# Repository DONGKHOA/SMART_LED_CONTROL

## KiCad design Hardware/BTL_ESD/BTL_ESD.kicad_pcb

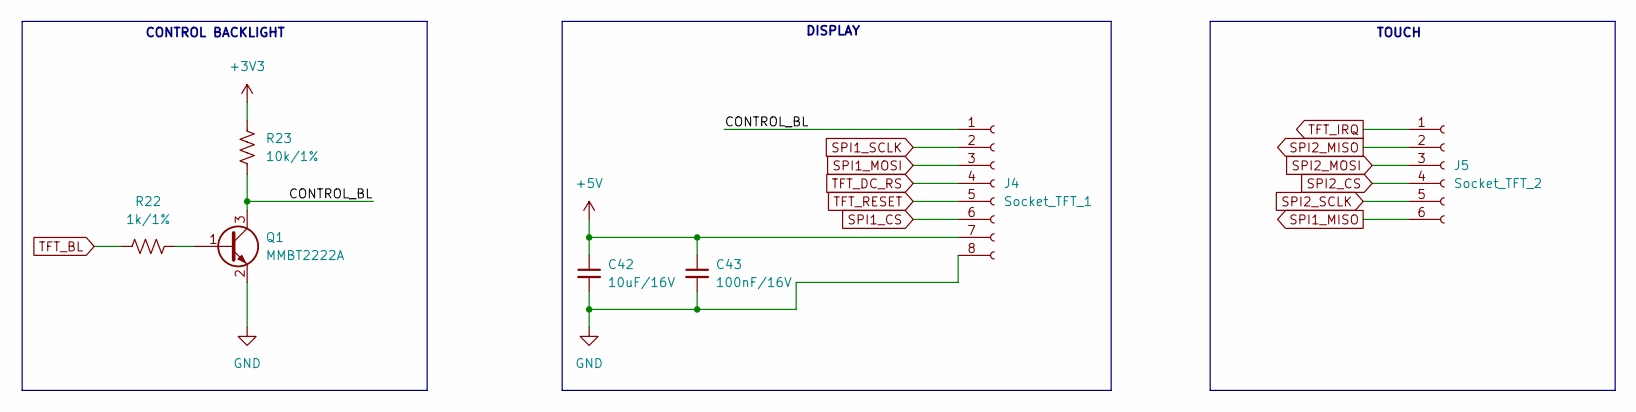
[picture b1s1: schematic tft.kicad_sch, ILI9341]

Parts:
C42: 10uF/16V; C_0603_1608Metric_Pad1.08x0.95mm_HandSolder
C43: 100nF/16V; C_0603_1608Metric_Pad1.08x0.95mm_HandSolder
J4: Socket_TFT_1; au_XH_2.54mm_8_Chan_Dan_SMD_Nam_Ngang
J5: Socket_TFT_2; au_XH_2.54mm_6_Chan_Dan_SMD_Nam_Ngang
Q1: MMBT2222A; SOT103P240X110-3N
R22: 1k/1%; R_0603_1608Metric_Pad0.98x0.95mm_HandSolder
R23: 10k/1%; R_0603_1608Metric_Pad0.98x0.95mm_HandSolder

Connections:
+3V3: R23.1; also elsewhere on the board
+5V: C42.1, C43.1, J4.7; also elsewhere on the board
/TFT/CONTROL_BL: J4.1, Q1.3, R23.2
GND: C42.2, C43.2, J4.8, Q1.2; also elsewhere on the board
unnamed: Q1.1, R22.2
SPI1_CS: J4.6; also elsewhere on the board
SPI1_MISO: J5.6; also elsewhere on the board
SPI1_MOSI: J4.3; also elsewhere on the board
SPI1_SCLK: J4.2; also elsewhere on the board
SPI2_CS: J5.4; also elsewhere on the board
SPI2_MISO: J5.2; also elsewhere on the board
SPI2_MOSI: J5.3; also elsewhere on the board
SPI2_SCLK: J5.5; also elsewhere on the board
TFT_BL: R22.1; also elsewhere on the board
TFT_DC_RS: J4.4; also elsewhere on the board
TFT_IRQ: J5.1; also elsewhere on the board
TFT_RESET: J4.5; also elsewhere on the board

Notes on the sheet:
TOUCH
DISPLAY
CONTROL BACKLIGHT

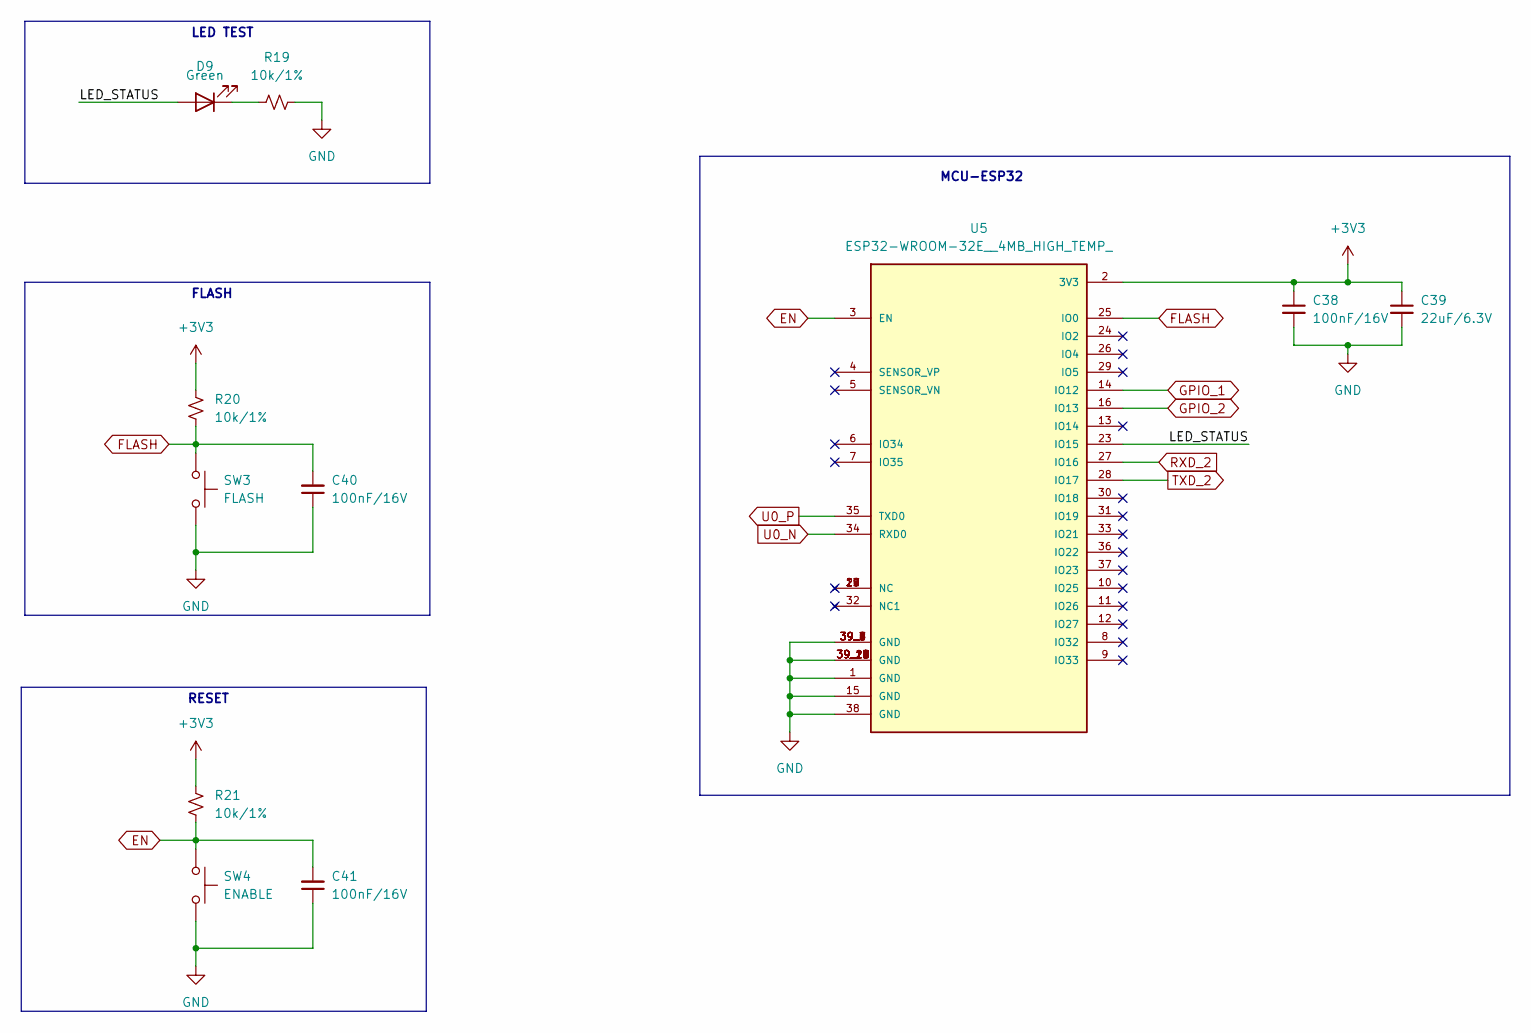
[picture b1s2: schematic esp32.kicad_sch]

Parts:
C38, C40, C41: 100nF/16V; C_0603_1608Metric_Pad1.08x0.95mm_HandSolder
C39: 22uF/6.3V; C_0603_1608Metric_Pad1.08x0.95mm_HandSolder
D9: Green; LED_0805_2012Metric_Pad1.15x1.40mm_HandSolder
R19, R20, R21: 10k/1%; R_0603_1608Metric_Pad0.98x0.95mm_HandSolder
SW3: FLASH; SW_SPST_B3U-1000P
SW4: ENABLE; SW_SPST_B3U-1000P
U5: ESP32-WROOM-32E__4MB_HIGH_TEMP_; XCVR_ESP32-WROOM-32E__4MB_HIGH_TEMP_

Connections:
+3V3: C38.1, C39.1, R20.1, R21.1, U5.2 (3V3); also elsewhere on the board
/ESP32/LED_STATUS: D9.2 (A), U5.23 (IO15)
EN: C41.2, R21.2, SW4.1, U5.3 (EN); also elsewhere on the board
FLASH: C40.2, R20.2, SW3.1, U5.25 (IO0); also elsewhere on the board
GND: C38.2, C39.2, C40.1, C41.1, R19.2, SW3.2, SW4.2, U5.1 (GND), U5.15 (GND), U5.38 (GND), U5.39_1 (GND), U5.39_2 (GND), U5.39_3 (GND), U5.39_4 (GND), U5.39_5 (GND), U5.39_6 (GND), U5.39_7 (GND), U5.39_8 (GND), U5.39_9 (GND), U5.39_10 (GND), U5.39_11 (GND), U5.39_12 (GND), U5.39_13 (GND), U5.39_14 (GND), U5.39_15 (GND), U5.39_16 (GND), U5.39_17 (GND), U5.39_18 (GND), U5.39_19 (GND), U5.39_20 (GND), U5.39_21 (GND); also elsewhere on the board
GPIO_1: U5.14 (IO12); also elsewhere on the board
GPIO_2: U5.16 (IO13); also elsewhere on the board
unnamed: D9.1 (K), R19.1
RXD_2: U5.27 (IO16); also elsewhere on the board
TXD_2: U5.28 (IO17); also elsewhere on the board
U0_N: U5.34 (RXD0); also elsewhere on the board
U0_P: U5.35 (TXD0); also elsewhere on the board

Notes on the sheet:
MCU-ESP32
LED TEST
RESET
FLASH

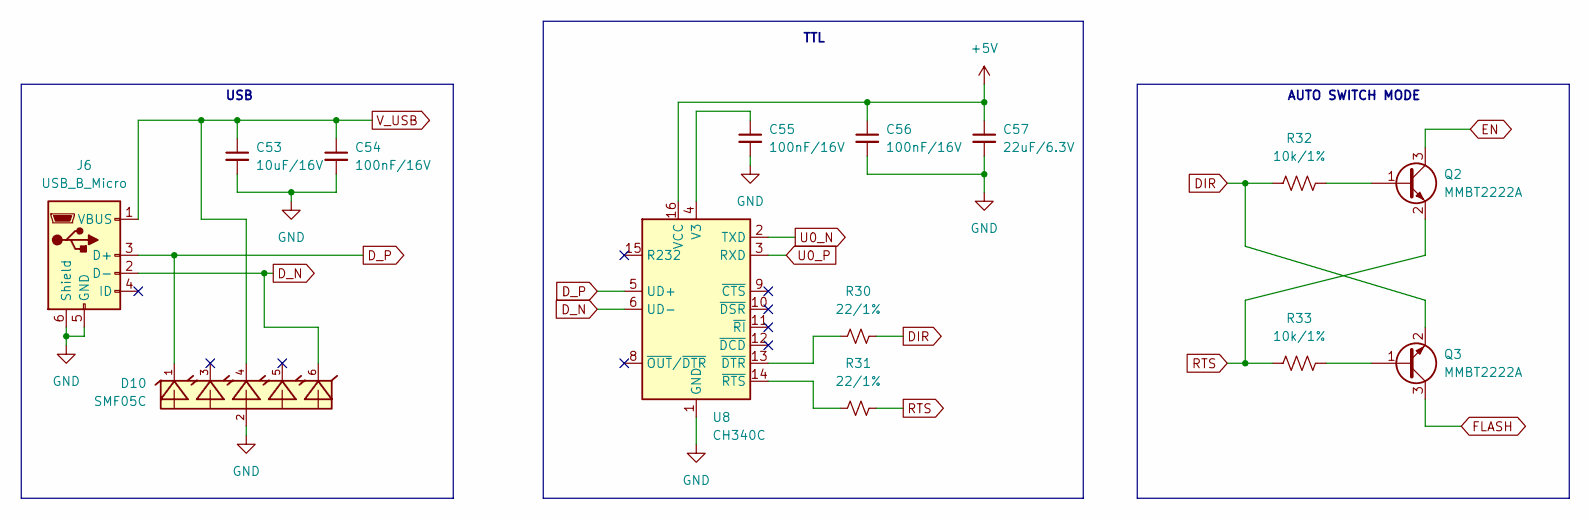
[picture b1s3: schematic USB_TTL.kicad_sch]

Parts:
C53: 10uF/16V; C_0603_1608Metric_Pad1.08x0.95mm_HandSolder
C54, C55, C56: 100nF/16V; C_0603_1608Metric_Pad1.08x0.95mm_HandSolder
C57: 22uF/6.3V; C_0603_1608Metric_Pad1.08x0.95mm_HandSolder
D10: SMF05C; SC70-6
J6: USB_B_Micro; USB_Micro-B_Wuerth_629105150521
Q2, Q3: MMBT2222A; SOT103P240X110-3N
R30, R31: 22/1%; R_0603_1608Metric_Pad0.98x0.95mm_HandSolder
R32, R33: 10k/1%; R_0603_1608Metric_Pad0.98x0.95mm_HandSolder
U8: CH340C; SOIC-16_3.9x9.9mm_P1.27mm

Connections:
+5V: C56.1, C57.1, U8.16 (VCC); also elsewhere on the board
DIR: Q3.2, R30.2, R32.1
D_N: D10.6, J6.2 (D-), U8.6 (UD-)
D_P: D10.1, J6.3 (D+), U8.5 (UD+)
EN: Q2.3; also elsewhere on the board
FLASH: Q3.3; also elsewhere on the board
GND: C53.2, C54.2, C55.2, C56.2, C57.2, D10.2, J6.5 (GND), J6.6 (Shield), U8.1 (GND); also elsewhere on the board
unnamed: Q2.1, R32.2
unnamed: Q3.1, R33.2
unnamed: C55.1, U8.4 (V3)
unnamed: R30.1, U8.13 (~DTR)
unnamed: R31.1, U8.14 (~RTS)
RTS: Q2.2, R31.2, R33.1
U0_N: U8.2 (TXD); also elsewhere on the board
U0_P: U8.3 (RXD); also elsewhere on the board
V_USB: C53.1, C54.1, D10.4, J6.1 (VBUS); also elsewhere on the board

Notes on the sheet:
TTL
AUTO SWITCH MODE
USB

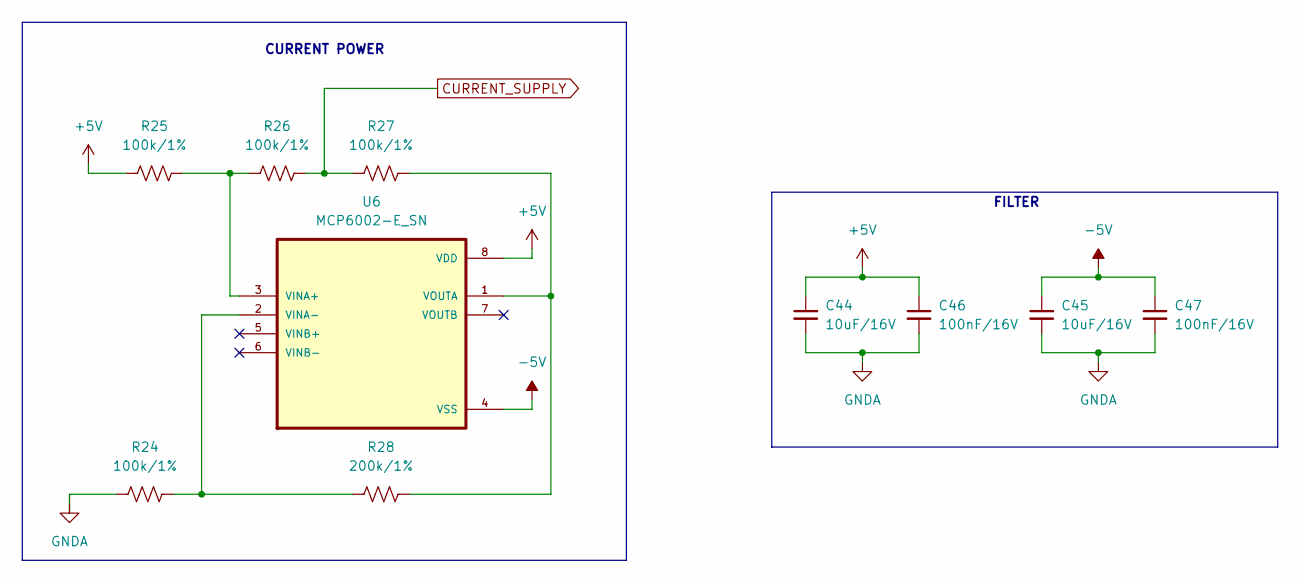
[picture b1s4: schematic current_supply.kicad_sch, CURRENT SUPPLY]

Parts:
C44, C45: 10uF/16V; C_0603_1608Metric_Pad1.08x0.95mm_HandSolder
C46, C47: 100nF/16V; C_0603_1608Metric_Pad1.08x0.95mm_HandSolder
R24, R25, R26, R27: 100k/1%; R_0603_1608Metric_Pad0.98x0.95mm_HandSolder
R28: 200k/1%; R_0603_1608Metric_Pad0.98x0.95mm_HandSolder
U6: MCP6002-E_SN; SOIC127P599X175-8N

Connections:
+5V: C44.1, C46.1, R25.1, U6.8 (VDD); also elsewhere on the board
-5V: C45.1, C47.1, U6.4 (VSS); also elsewhere on the board
CURRENT_SUPPLY: R26.2, R27.1; also elsewhere on the board
GNDA: C44.2, C45.2, C46.2, C47.2, R24.1; also elsewhere on the board
unnamed: R25.2, R26.1, U6.3 (VINA+)
unnamed: R24.2, R28.1, U6.2 (VINA-)
unnamed: R27.2, R28.2, U6.1 (VOUTA)

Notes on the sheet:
CURRENT POWER
FILTER

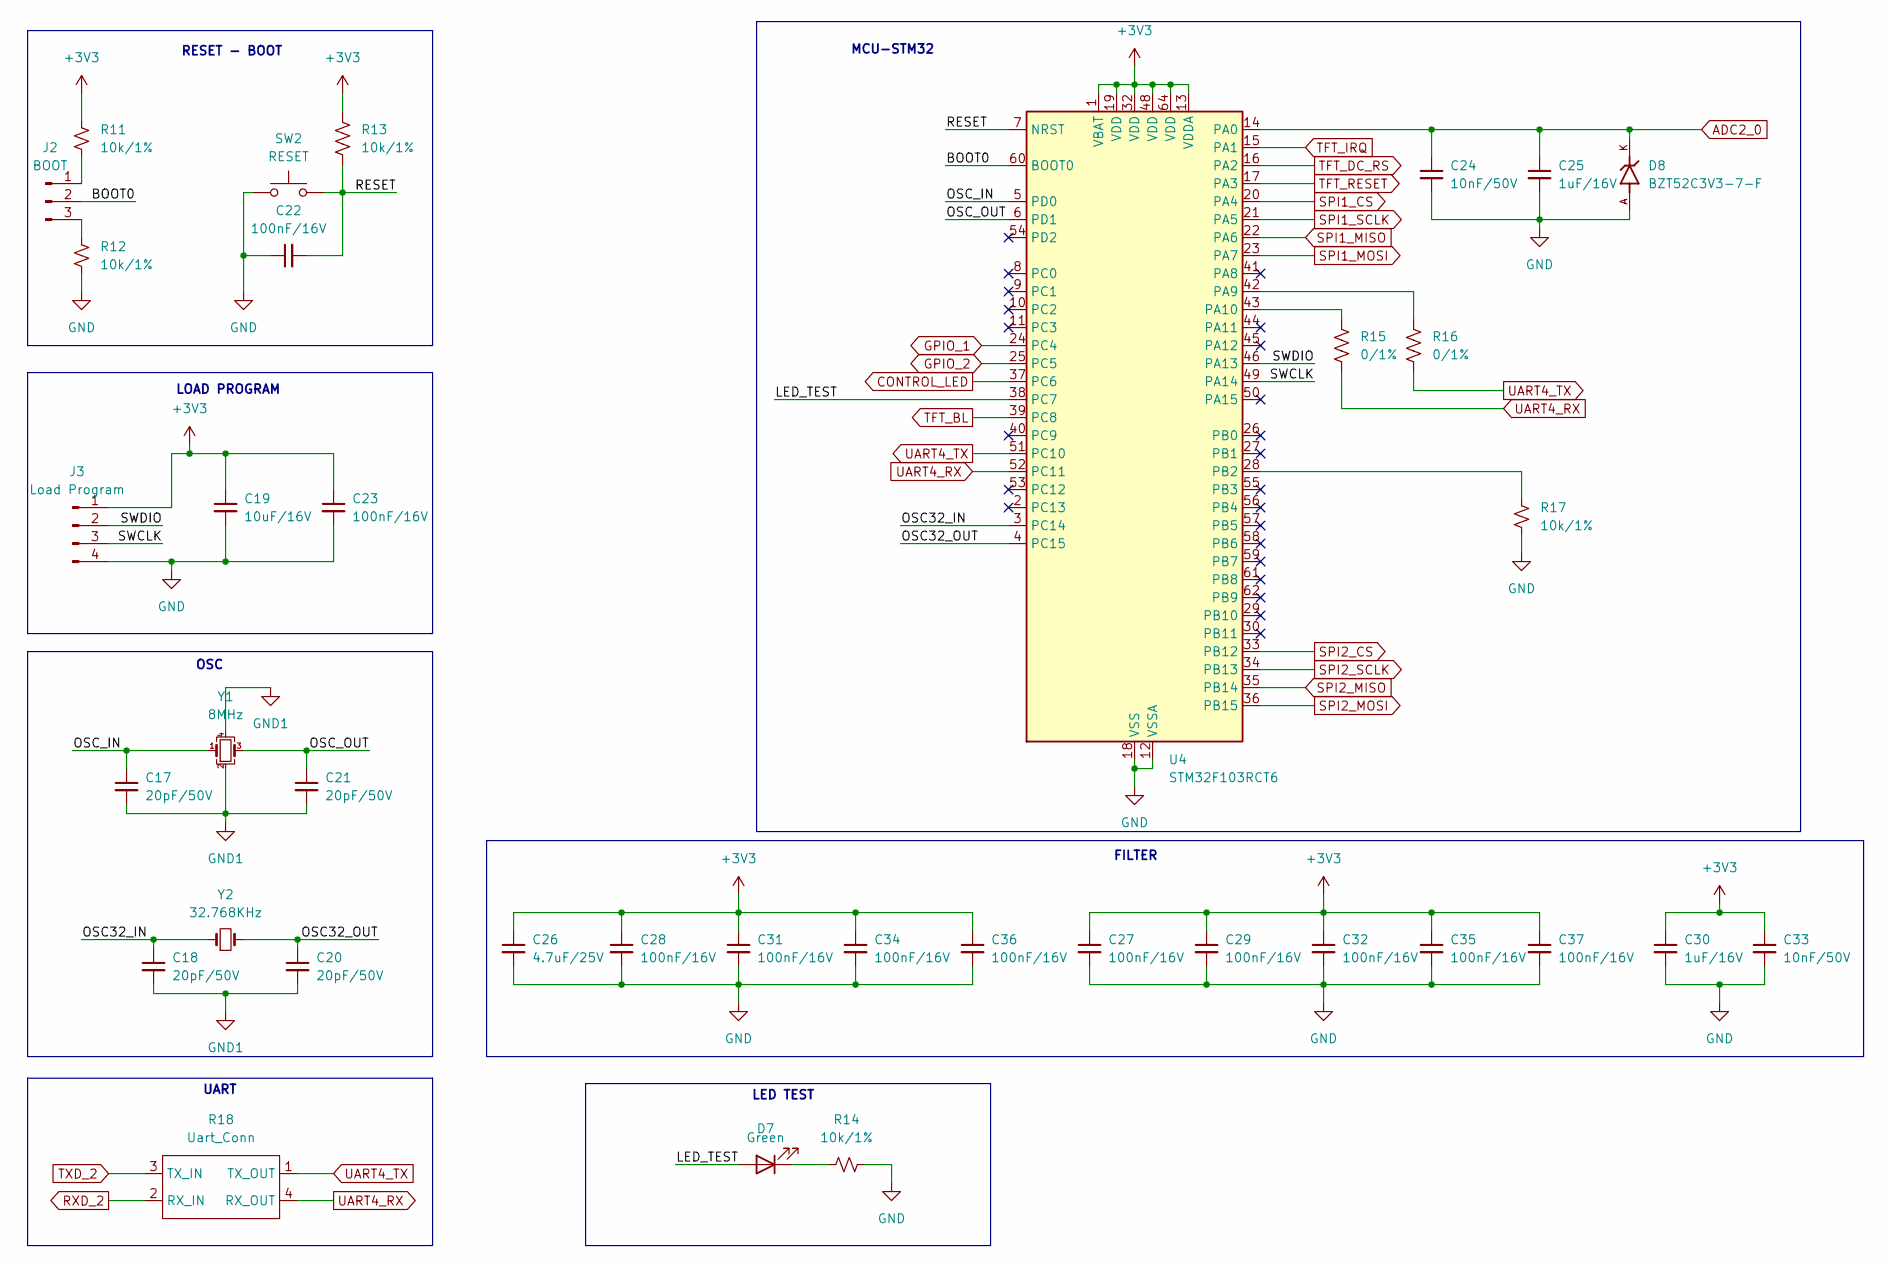
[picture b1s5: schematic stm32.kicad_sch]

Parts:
C17, C18, C20, C21: 20pF/50V; C_0603_1608Metric_Pad1.08x0.95mm_HandSolder
C19: 10uF/16V; C_0603_1608Metric_Pad1.08x0.95mm_HandSolder
C22, C23, C27, C28, C29, C31, C32, C34, C35, C36, C37: 100nF/16V; C_0603_1608Metric_Pad1.08x0.95mm_HandSolder
C24, C33: 10nF/50V; C_0603_1608Metric_Pad1.08x0.95mm_HandSolder
C25, C30: 1uF/16V; C_0603_1608Metric_Pad1.08x0.95mm_HandSolder
C26: 4.7uF/25V; C_0603_1608Metric_Pad1.08x0.95mm_HandSolder
D7: Green; LED_0805_2012Metric_Pad1.15x1.40mm_HandSolder
D8: BZT52C3V3-7-F; BZT52C3V3
J2: BOOT; PinHeader_1x03_P2.54mm_Vertical
J3: Load Program; PinHeader_1x04_P2.54mm_Vertical
R11, R12, R13, R14, R17: 10k/1%; R_0603_1608Metric_Pad0.98x0.95mm_HandSolder
R15, R16: 0/1%; R_0603_1608Metric_Pad0.98x0.95mm_HandSolder
R18: Uart_Conn; uart_conn
SW2: RESET; SW_SPST_B3U-1000P
U4: STM32F103RCT6; LQFP-64_10x10mm_P0.5mm
Y1: 8MHz; Crystal_SMD_EuroQuartz_MQ-4Pin_7.0x5.0mm
Y2: 32.768KHz; Crystal_SMD_3215-2Pin_3.2x1.5mm

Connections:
+3V3: C19.1, C23.1, C26.1, C27.1, C28.1, C29.1, C30.1, C31.1, C32.1, C33.1, C34.1, C35.1, C36.1, C37.1, J3.1, R11.1, R13.1, U4.1 (VBAT), U4.13 (VDDA), U4.19 (VDD), U4.32 (VDD), U4.48 (VDD), U4.64 (VDD); also elsewhere on the board
/STM32/BOOT0: J2.2, U4.60 (BOOT0)
/STM32/LED_TEST: D7.2 (A), U4.38 (PC7)
/STM32/OSC32_IN: C18.1, U4.3 (PC14), Y2.1
/STM32/OSC32_OUT: C20.1, U4.4 (PC15), Y2.2
/STM32/OSC_IN: C17.1, U4.5 (PD0), Y1.1
/STM32/OSC_OUT: C21.1, U4.6 (PD1), Y1.3
/STM32/RESET: C22.2, R13.2, SW2.2, U4.7 (NRST)
/STM32/SWCLK: J3.3, U4.49 (PA14)
/STM32/SWDIO: J3.2, U4.46 (PA13)
ADC1_0: C24.1, C25.1, D8.K, U4.14 (PA0); also elsewhere on the board
CONTROL_LED: U4.37 (PC6); also elsewhere on the board
GND: C19.2, C22.1, C23.2, C24.2, C25.2, C26.2, C27.2, C28.2, C29.2, C30.2, C31.2, C32.2, C33.2, C34.2, C35.2, C36.2, C37.2, D8.A, J3.4, R12.2, R14.2, R17.2, SW2.1, U4.12 (VSSA), U4.18 (VSS), U4.31 (VSS), U4.47 (VSS), U4.63 (VSS); also elsewhere on the board
GND1: C17.2, C18.2, C20.2, C21.2, Y1.2, Y1.4; also elsewhere on the board
GPIO_1: U4.24 (PC4); also elsewhere on the board
GPIO_2: U4.25 (PC5); also elsewhere on the board
unnamed: D7.1 (K), R14.1
unnamed: J2.1, R11.2
unnamed: J2.3, R12.1
unnamed: R16.1, U4.42 (PA9)
unnamed: R15.1, U4.43 (PA10)
unnamed: R17.1, U4.28 (PB2)
RXD_2: R18.2 (RX_IN); also elsewhere on the board
SPI1_CS: U4.20 (PA4); also elsewhere on the board
SPI1_MISO: U4.22 (PA6); also elsewhere on the board
SPI1_MOSI: U4.23 (PA7); also elsewhere on the board
SPI1_SCLK: U4.21 (PA5); also elsewhere on the board
SPI2_CS: U4.33 (PB12); also elsewhere on the board
SPI2_MISO: U4.35 (PB14); also elsewhere on the board
SPI2_MOSI: U4.36 (PB15); also elsewhere on the board
SPI2_SCLK: U4.34 (PB13); also elsewhere on the board
TFT_BL: U4.39 (PC8); also elsewhere on the board
TFT_DC_RS: U4.16 (PA2); also elsewhere on the board
TFT_IRQ: U4.15 (PA1); also elsewhere on the board
TFT_RESET: U4.17 (PA3); also elsewhere on the board
TXD_2: R18.3 (TX_IN); also elsewhere on the board
UART4_RX: R15.2, R18.4 (RX_OUT), U4.52 (PC11)
UART4_TX: R16.2, R18.1 (TX_OUT), U4.51 (PC10)

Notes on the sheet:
UART
MCU-STM32
FILTER
OSC
RESET - BOOT
LOAD PROGRAM
LED TEST

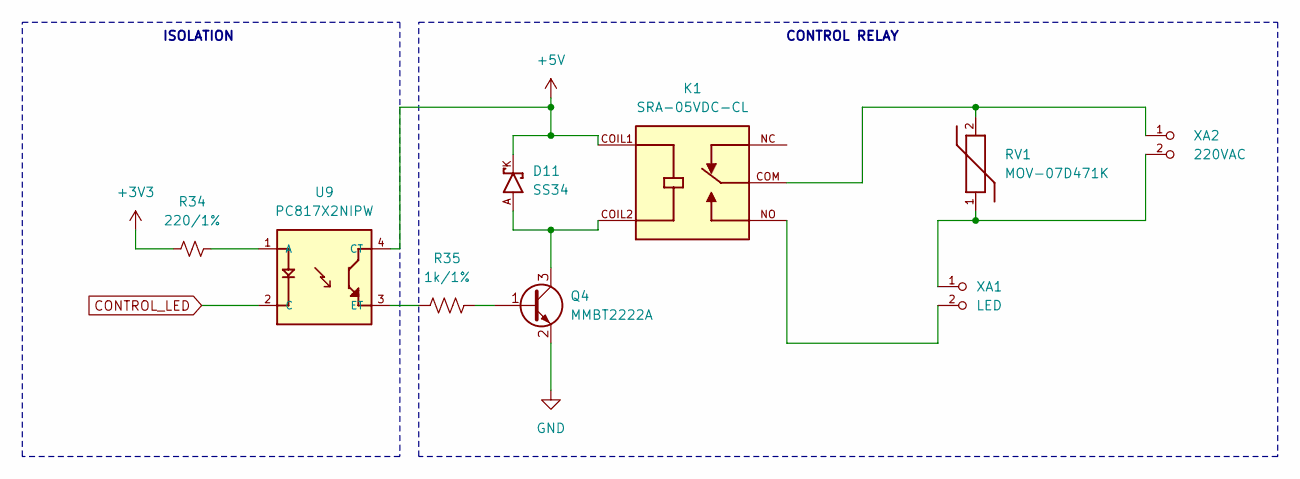
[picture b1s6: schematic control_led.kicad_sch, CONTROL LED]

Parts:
D11: SS34; DO-214AC
K1: SRA-05VDC-CL; RELAY_SRA-05VDC-CL
Q4: MMBT2222A; SOT103P240X110-3N
R34: 220/1%; R_0603_1608Metric_Pad0.98x0.95mm_HandSolder
R35: 1k/1%; R_0603_1608Metric_Pad0.98x0.95mm_HandSolder
RV1: MOV-07D471K; MOV07D471K
U9: PC817X2NIPW; SOT254P975X400-4N
XA1: LED; PHOENIX_MKDS1_2-3.81
XA2: 220VAC; PHOENIX_MKDS1_2-3.81

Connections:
+3V3: R34.1; also elsewhere on the board
+5V: D11.K, K1.COIL1, U9.4 (CT); also elsewhere on the board
CONTROL_LED: U9.2 (C); also elsewhere on the board
GND: Q4.2; also elsewhere on the board
unnamed: D11.A, K1.COIL2, Q4.3
unnamed: K1.COM, RV1.2, XA2.1
unnamed: K1.NO, XA1.2
unnamed: Q4.1, R35.2
unnamed: RV1.1, XA1.1, XA2.2
unnamed: R34.2, U9.1 (A)
unnamed: R35.1, U9.3 (ET)

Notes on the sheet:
ISOLATION
CONTROL RELAY

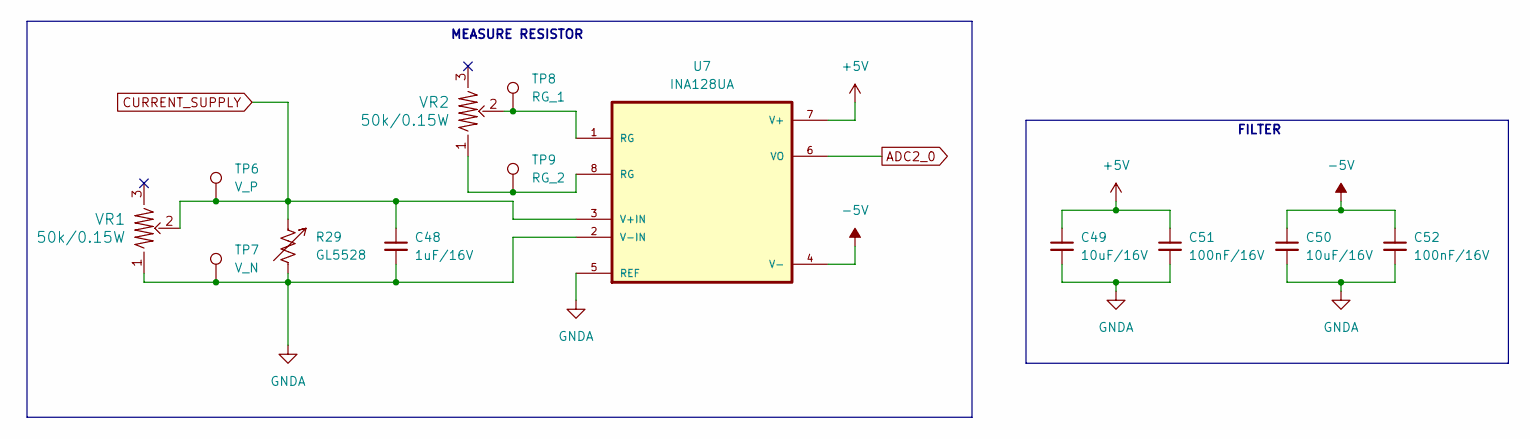
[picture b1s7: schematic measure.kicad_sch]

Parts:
C48: 1uF/16V; C_0603_1608Metric_Pad1.08x0.95mm_HandSolder
C49, C50: 10uF/16V; C_0603_1608Metric_Pad1.08x0.95mm_HandSolder
C51, C52: 100nF/16V; C_0603_1608Metric_Pad1.08x0.95mm_HandSolder
R29: GL5528; R_LDR_5.0x4.1mm_P3mm_Vertical
TP6: V_P; TestPoint_Pad_D2.5mm
TP7: V_N; TestPoint_Pad_D2.5mm
TP8: RG_1; TestPoint_Pad_D2.5mm
TP9: RG_2; TestPoint_Pad_D2.5mm
U7: INA128UA; SOIC127P599X175-8N
VR1, VR2: 50k/0.15W; EVM-3E

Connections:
+5V: C49.1, C51.1, U7.7 (V+); also elsewhere on the board
-5V: C50.1, C52.1, U7.4 (V-); also elsewhere on the board
ADC1_0: U7.6 (VO); also elsewhere on the board
CURRENT_SUPPLY: C48.1, R29.1, TP6.1, U7.3 (V+IN), VR1.2; also elsewhere on the board
GNDA: C48.2, C49.2, C50.2, C51.2, C52.2, R29.2, TP7.1, U7.2 (V-IN), U7.5 (REF), VR1.1; also elsewhere on the board
unnamed: TP8.1, U7.1 (RG), VR2.2
unnamed: TP9.1, U7.8 (RG), VR2.1

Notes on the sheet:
MEASURE RESISTOR
FILTER

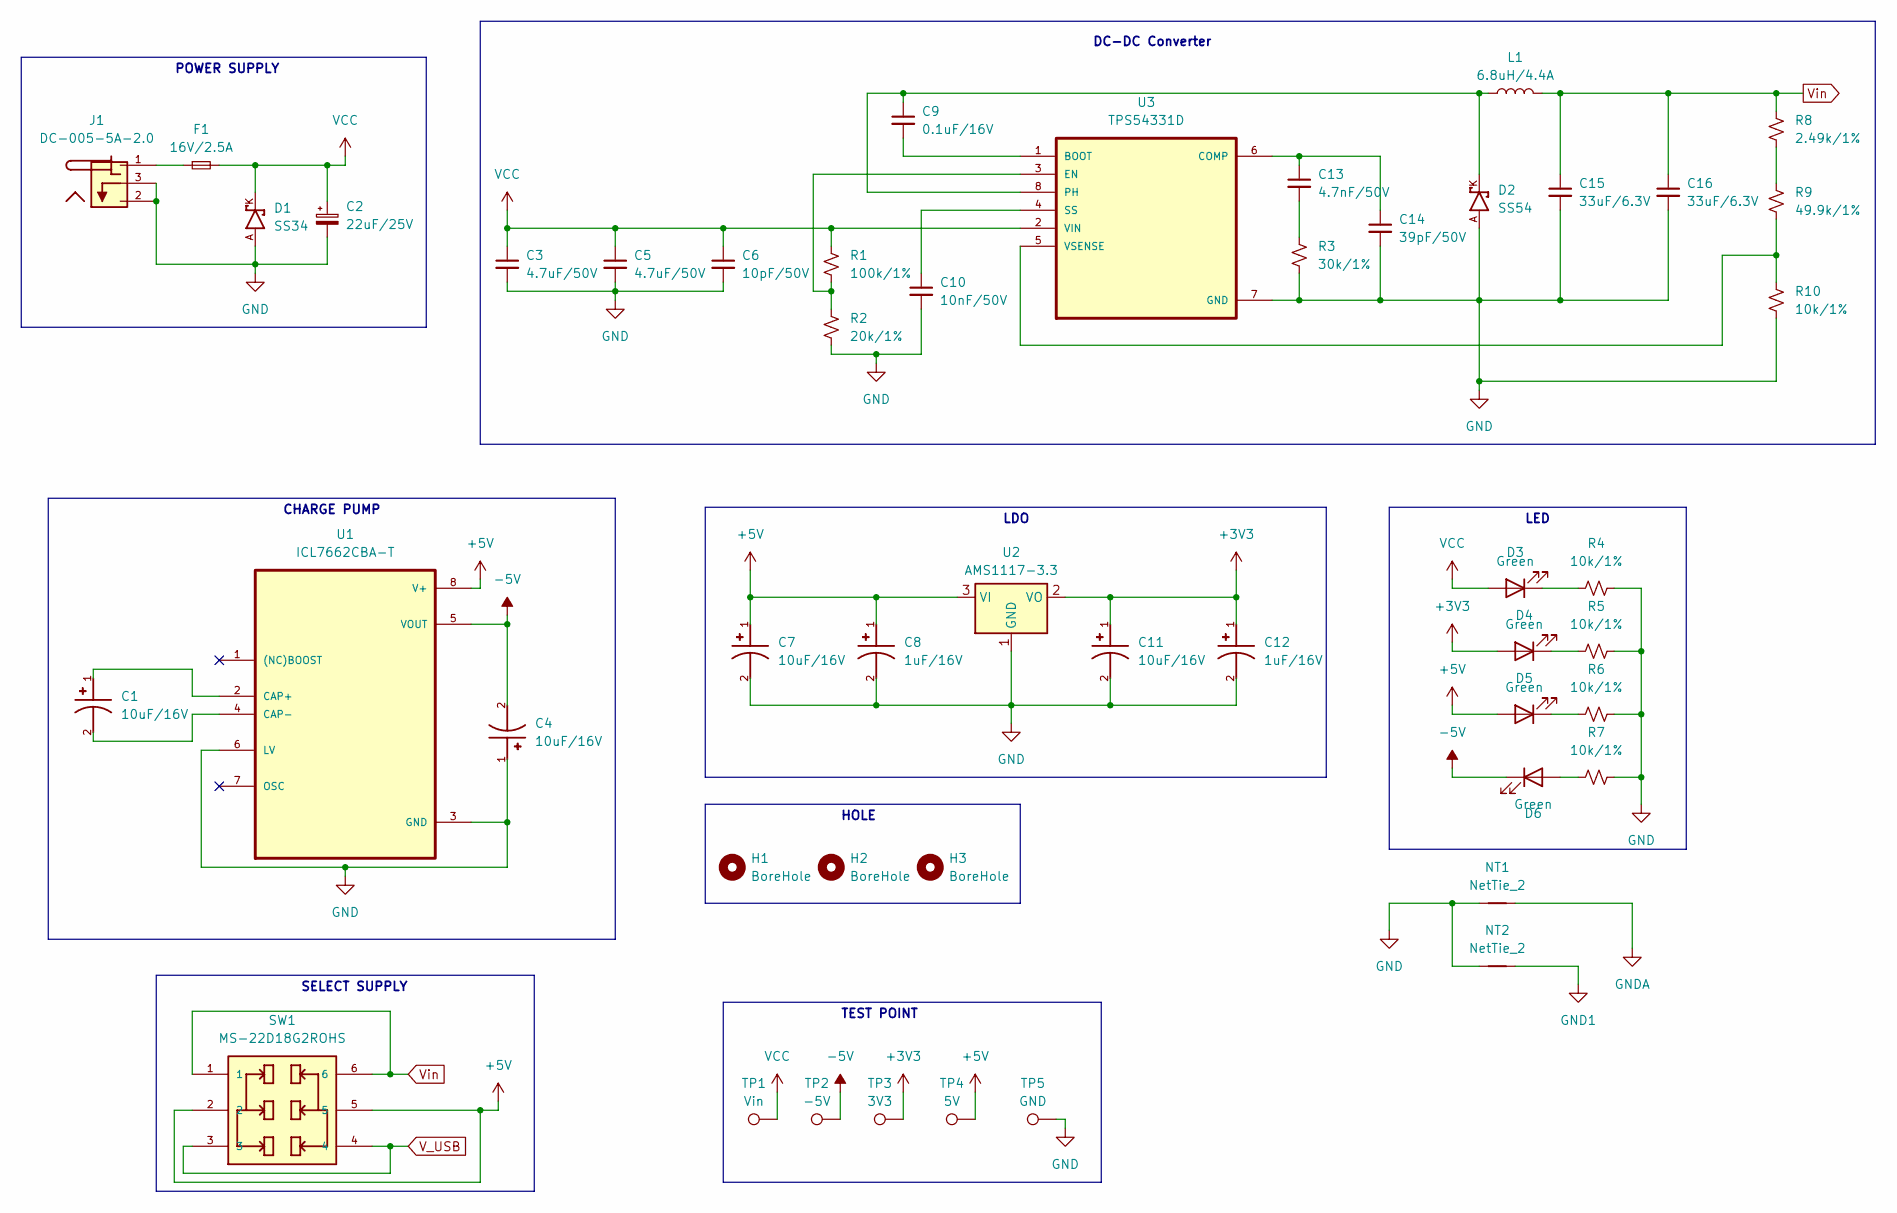
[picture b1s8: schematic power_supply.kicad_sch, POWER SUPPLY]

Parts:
C1, C4, C7, C11: 10uF/16V; CAPMP3216X180N
C2: 22uF/25V; CP_Elec_6.3x5.4
C3, C5: 4.7uF/50V; C_0805_2012Metric_Pad1.18x1.45mm_HandSolder
C6: 10pF/50V; C_0805_2012Metric_Pad1.18x1.45mm_HandSolder
C8, C12: 1uF/16V; CAPMP3216X180N
C9: 0.1uF/16V; C_0603_1608Metric_Pad1.08x0.95mm_HandSolder
C10: 10nF/50V; C_0603_1608Metric_Pad1.08x0.95mm_HandSolder
C13: 4.7nF/50V; C_0603_1608Metric_Pad1.08x0.95mm_HandSolder
C14: 39pF/50V; C_0603_1608Metric_Pad1.08x0.95mm_HandSolder
C15, C16: 33uF/6.3V; C_0805_2012Metric_Pad1.18x1.45mm_HandSolder
D1: SS34; DO-214AC
D2: SS54; DO-214AC
D3, D4, D5, D6: Green; LED_0805_2012Metric_Pad1.15x1.40mm_HandSolder
F1: 16V/2.5A; Fuse_1812_4532Metric_Pad1.30x3.40mm_HandSolder
H1, H2, H3: BoreHole; MountingHole_3.2mm_M3_Pad_TopBottom
J1: DC-005-5A-2.0; XKB_DC-005-5A-2.0
L1: 6.8uH/4.4A; CDRH8D43NP-6R8
NT1: NetTie_2; NetTie-2_SMD_Pad2.0mm
NT2: NetTie_2; NetTie-2_SMD_Pad0.5mm
R1: 100k/1%; R_0603_1608Metric_Pad0.98x0.95mm_HandSolder
R2: 20k/1%; R_0603_1608Metric_Pad0.98x0.95mm_HandSolder
R3: 30k/1%; R_0603_1608Metric_Pad0.98x0.95mm_HandSolder
R4, R5, R6, R7, R10: 10k/1%; R_0603_1608Metric_Pad0.98x0.95mm_HandSolder
R8: 2.49k/1%; R_0603_1608Metric_Pad0.98x0.95mm_HandSolder
R9: 49.9k/1%; R_0603_1608Metric_Pad0.98x0.95mm_HandSolder
SW1: MS-22D18G2ROHS; SW_MS-22D18G2ROHS
TP1: Vin; TestPoint_Pad_D2.5mm
TP2: -5V; TestPoint_Pad_D2.5mm
TP3: 3V3; TestPoint_Pad_D2.5mm
TP4: 5V; TestPoint_Pad_D2.5mm
TP5: GND; TestPoint_Pad_D2.5mm
U1: ICL7662CBA-T; SOIC127P600X175-8N
U2: AMS1117-3.3; SOT-223-3_TabPin2
U3: TPS54331D; SOIC127P599X175-8N

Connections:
+3V3: C11.1, C12.1, D4.2 (A), TP3.1, U2.2 (VO); also elsewhere on the board
+5V: C7.1, C8.1, D5.2 (A), SW1.2, SW1.5, TP4.1, U1.8 (V+), U2.3 (VI); also elsewhere on the board
-5V: C4.2, D6.1 (K), TP2.1, U1.5 (VOUT); also elsewhere on the board
GND: C2.2, C3.2, C4.1, C5.2, C6.2, C7.2, C8.2, C10.2, C11.2, C12.2, C14.2, C15.2, C16.2, D1.A, D2.A, J1.2, J1.3, NT1.1, NT2.1, R2.2, R3.2, R4.2, R5.2, R6.2, R7.2, R10.2, TP5.1, U1.3 (GND), U1.6 (LV), U2.1 (GND), U3.7 (GND); also elsewhere on the board
GND1: NT2.2; also elsewhere on the board
GNDA: NT1.2; also elsewhere on the board
unnamed: C13.2, R3.1
unnamed: D3.1 (K), R4.1
unnamed: D4.1 (K), R5.1
unnamed: D5.1 (K), R6.1
unnamed: D6.2 (A), R7.1
unnamed: F1.1, J1.1
unnamed: R8.2, R9.1
unnamed: C1.1, U1.2 (CAP+)
unnamed: C1.2, U1.4 (CAP-)
unnamed: C9.2, U3.1 (BOOT)
unnamed: C13.1, C14.1, U3.6 (COMP)
unnamed: R1.2, R2.1, U3.3 (EN)
unnamed: C9.1, D2.K, L1.1, U3.8 (PH)
unnamed: C10.1, U3.4 (SS)
unnamed: R9.2, R10.1, U3.5 (VSENSE)
VCC: C2.1, C3.1, C5.1, C6.1, D1.K, D3.2 (A), F1.2, R1.1, TP1.1, U3.2 (VIN)
V_USB: SW1.3, SW1.4; also elsewhere on the board
Vin: C15.1, C16.1, L1.2, R8.1, SW1.1, SW1.6

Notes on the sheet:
DC-DC Converter
CHARGE PUMP
SELECT SUPPLY
LDO
HOLE
POWER SUPPLY
TEST POINT
LED

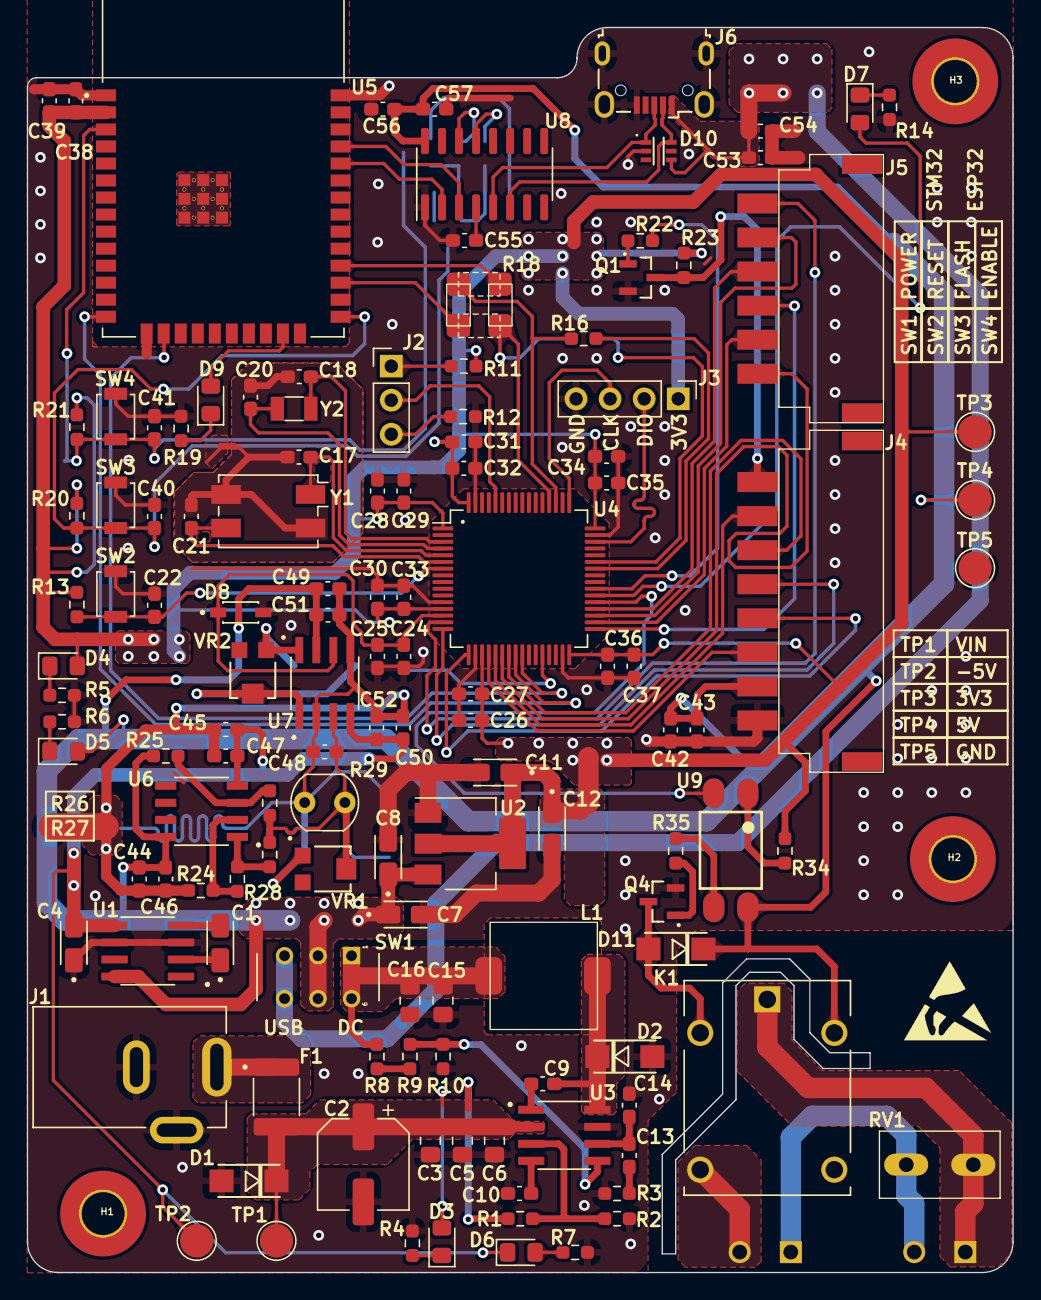
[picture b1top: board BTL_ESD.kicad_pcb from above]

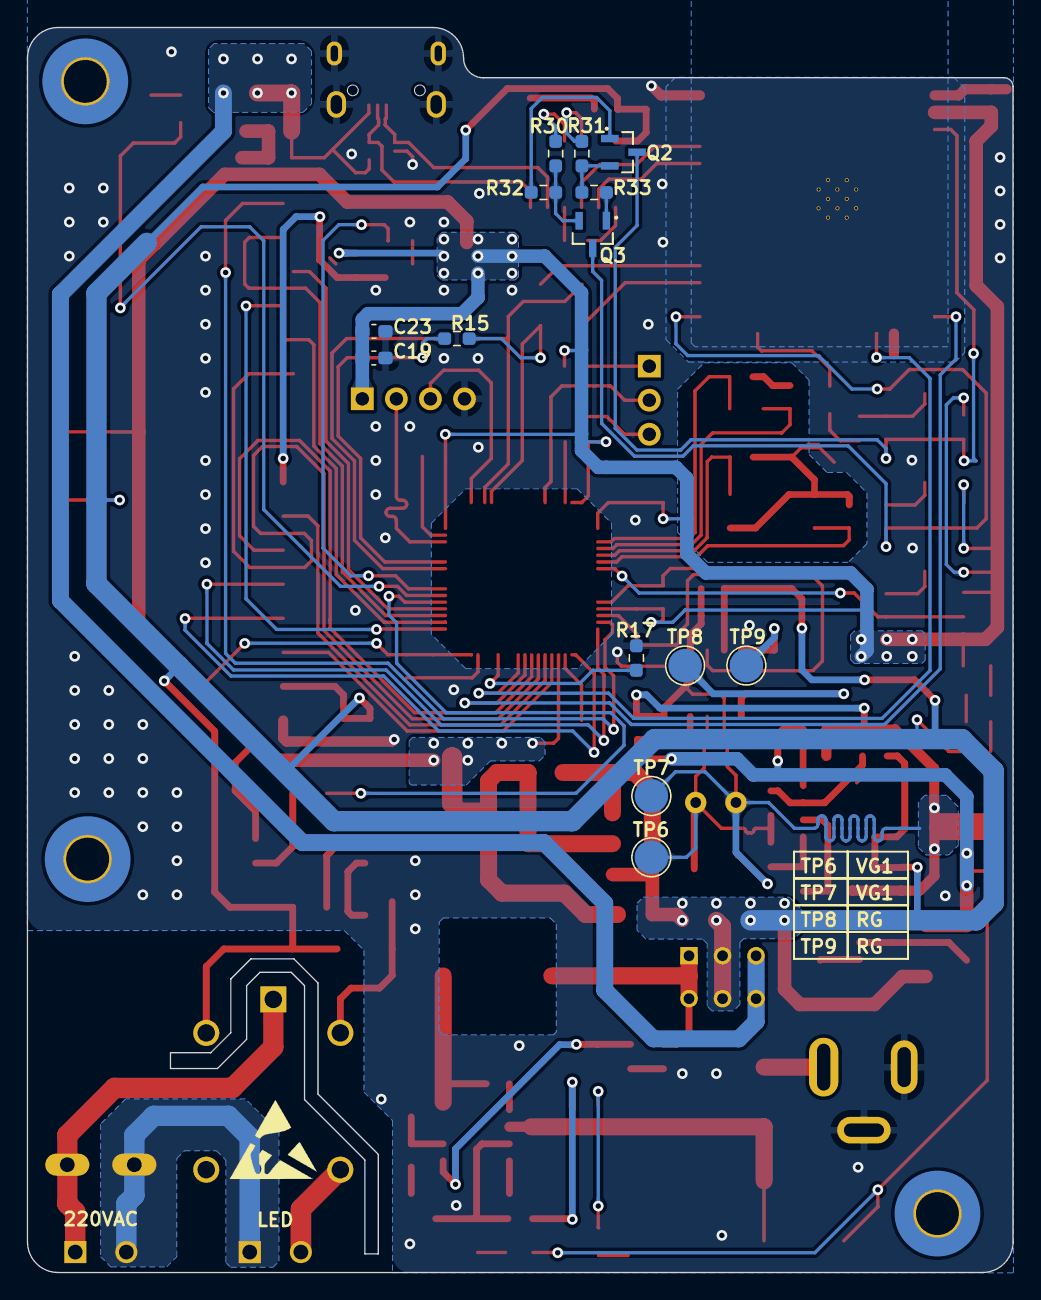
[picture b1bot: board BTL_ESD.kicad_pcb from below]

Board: 2 copper layers, 73.5 x 92.8 mm, 150 parts (14 on the bottom side), 89 nets.

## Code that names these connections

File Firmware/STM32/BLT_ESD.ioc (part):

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Mcu.Name=STM32F103R(C-D-E)Tx
Mcu.Package=LQFP64
Mcu.UserName=STM32F103RCTx
PA0-WKUP.Signal=ADCx_IN0
PA1.Signal=GPIO_Input
PA13.Mode=Serial_Wire
PA13.Signal=SYS_JTMS-SWDIO
PA14.Mode=Serial_Wire
PA14.Signal=SYS_JTCK-SWCLK
PA2.GPIOParameters=GPIO_Speed,GPIO_Label
PA2.GPIO_Label=TFT_DC_RS
PA2.GPIO_Speed=GPIO_SPEED_FREQ_MEDIUM
PA2.Signal=GPIO_Output
PA3.GPIOParameters=GPIO_Speed,GPIO_Label
PA3.GPIO_Label=TFT_RESET
PA3.GPIO_Speed=GPIO_SPEED_FREQ_MEDIUM
PA3.Signal=GPIO_Output
PA4.Mode=NSS_Signal_Hard_Output
PA4.Signal=SPI1_NSS
PA5.Mode=Full_Duplex_Master
PA5.Signal=SPI1_SCK
PA6.Mode=Full_Duplex_Master
PA6.Signal=SPI1_MISO
PA7.Mode=Full_Duplex_Master
PA7.Signal=SPI1_MOSI
PB12.Mode=NSS_Signal_Hard_Output
PB12.Signal=SPI2_NSS
PB13.Mode=Full_Duplex_Master
PB13.Signal=SPI2_SCK
PB14.Mode=Full_Duplex_Master
PB14.Signal=SPI2_MISO
PB15.Mode=Full_Duplex_Master
PB15.Signal=SPI2_MOSI
PC10.Mode=Asynchronous
PC10.Signal=UART4_TX
PC11.Mode=Asynchronous
PC11.Signal=UART4_RX
PC6.GPIOParameters=PinState
PC6.PinState=GPIO_PIN_SET
PC6.Signal=GPIO_Output
PC7.Signal=GPIO_Output
PC8.Signal=GPIO_Output
PD0-OSC_IN.Mode=HSE-External-Oscillator
PD0-OSC_IN.Signal=RCC_OSC_IN
PD1-OSC_OUT.Mode=HSE-External-Oscillator
PD1-OSC_OUT.Signal=RCC_OSC_OUT
RCC.HSEDivPLL=RCC_HSE_PREDIV_DIV2
RCC.SYSCLKFreq_VALUE=60000000
RCC.SYSCLKSource=RCC_SYSCLKSOURCE_PLLCLK
board=custom

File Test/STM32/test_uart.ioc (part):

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Mcu.Name=STM32F103C(8-B)Tx
Mcu.Package=LQFP48
Mcu.UserName=STM32F103C8Tx
PA10.Mode=Asynchronous
PA10.Signal=USART1_RX
PA13.Mode=Serial_Wire
PA13.Signal=SYS_JTMS-SWDIO
PA14.Mode=Serial_Wire
PA14.Signal=SYS_JTCK-SWCLK
PA9.Mode=Asynchronous
PA9.Signal=USART1_TX
board=custom

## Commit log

2024-03-07 hardware:folder hardware: upload schematic power
2024-03-09 hardware: ver 1 schematic
2024-03-16 fea:STM32: upload structure fodler
2024-03-17 fix:STM32: update structure folder Libs
2024-03-17 hardware:update pcb track power
2024-03-17 code:ESP32: upload project folder
2024-03-17 fea:git: upload file gitignore
2024-03-18 code:stm32:update folder
2024-03-18 update_ioc
2024-03-19 file:STM32: update structure folder
2024-03-19 code:STM32: update structure file
2024-03-19 code:ESP32: update library wifi
2024-03-23 code:ESP32: update uart driver, main.c && hardware file pcb
2024-03-23 code:ESP32: add comment in file .c
2024-03-24 code:ESP32: update main and structure file libs
2024-03-26 code:esp32: update main
2024-03-30 code:esp32:update nvs, main, wifi
2024-03-31 fea:esp32/wifi: add store wifi in nvs, scan wifi in nvs
2024-03-31 cmt:esp32: add cmt
2024-04-01 code:esp32: update typdef
2024-04-02 Doc:README:upload frame tranmission
2024-04-02 code:esp32: update uart rx tx between esp32 and stm32
2024-04-04 code:README: update frame tran
2024-04-09 folder:firmware: add calib adc, adc driver, illuminance
2024-04-09 code:esp32:update main
2024-04-09 code:stm32: update format code
2024-04-10 update:esp32
2024-04-11 fea:stm32:add folder freertos
2024-04-11 test_screen
2024-04-11 test
2024-04-13 update:esp32: name project
2024-04-13 fea:stm32: add folder event ui
2024-04-13 path:stm32: add path lib ui_event and ui_screen
2024-04-14 update task screen
2024-04-14 test:esp32:scan wifi
2024-04-14 startup:stm32: update file start up
2024-04-14 update: delete monochormebitmap
2024-04-15 Create Temperature
2024-04-16 test:esp32: fix error duplicate ssid in wifi driver
2024-04-16 uart:stm32: add folder Utils from Baobuibk https://github.com/baobuibk/FreeRTOS_F4_Queue_InterTask
2024-04-16 code:esp32:update wifi driver and send frame data to stm32
2024-04-17 update_taskScreen
2024-04-17 code:stm32:add path include
2024-04-17 update main, libs
2024-04-20 code:stm32: add screen 5
2024-04-20 code:stm32:update file start up
2024-04-20 stm32: update: task_screen( add screen 5 and add icon )
2024-04-20 STM32: UI_EVENT: Update: Event_Screen_4
2024-04-21 update libs, main
2024-04-21 processing data:esp32: fix uart tx and mqtt
2024-04-21 STM32: Update: comment
2024-04-22 fea:stm32: update touch display
2024-04-22 screen2:stm32: update event
2024-04-24 update: stm32: complete icon
2024-04-24 cmt:stm32:add comment on function and variable
2024-04-25 flow system:stm32:update flow code in screen 2 and screen 3
2024-04-26 update adjust Ev
2024-04-27 Update: STM32: completed screen_task
2024-04-28 STM32: Uart_Rx_Task
2024-04-28 update uartTx_task in main
2024-04-28 edit MQTT, MQTT_pos in event_screen_5.c
2024-04-29 Move include lib from main.c to main.h
2024-04-29 update: STM32: UartRxTask & event_screen_6
2024-04-29 update hardware
2024-04-29 format main.c #STM32
2024-04-29 update_control_task
2024-04-29 fea:ESP32: update UART RX task
2024-04-29 fix:STM32: fix error compile
2024-04-29 fix:STM32: fix error float number in line 758
2024-04-30 edit variables check_state_auto/led in uartTx task and autocontrol_mode (illuminance)
2024-04-30 fix: STM32: define UartRx
2024-04-30 update: UartRxTask
2024-04-30 Update: STM32: add autocontrol_mode in adc_task
2024-05-01 update timer_read_temp in ADC_task
2024-05-01 Update: STM32: move xTimerStart of timer_read_temp
2024-05-02 update:STM32:screen 1 and screen 5
2024-05-02 STM32: edit illuminance_signal()
2024-05-02 update: cordinate icon in stm32
2024-05-02 STM32: Fix illuminance_signal() in illuminance.c
2024-05-02 STM32: edit previous_state in illuminance_signal()
2024-05-03 update cordinate icon
2024-05-05 event:stm32: update event screen 1
2024-05-05 update variable x, y
2024-05-05 fea:stm32: update fea auto led
2024-05-06 update esp32
2024-05-06 update screen 2 3 stm32
2024-05-06 update_screen_2
2024-05-06 update wifi
2024-05-07 mqtt:stm32:update flow control data
2024-05-07 update: stm32: screen_screentask
2024-05-07 update reading temperature and illuminance
2024-05-07 update: stm32
2024-05-07 update stm32
2024-05-07 update: stm32:
2024-05-07 update: stm32: hardfalt
2024-05-08 completed project V1
2024-05-09 release v1
2024-05-23 update ver 1
